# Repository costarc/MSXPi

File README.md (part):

# MSXPi

MSXPi is a hardware interface and software solution that lets MSX computers
control and use Raspberry Pi resources. The interface exposes I/O ports that
the MSX reads and writes, and the data appears on the Raspberry Pi side, where
a Python program (the *msxpi-server*) acts on it. Through it the MSX can reach
network drives, the internet, disk images, ROM archives, ChatGPT, an IRC
server, TCP/IP (via UNAPI) and the Raspberry Pi itself. A Raspberry Pi Zero W
or Zero 2 W is the recommended companion board.

MSXPi also exists as a virtual device for **openMSX**: the emulated MSX gets
the same commands and the same server, with no hardware at all. See
[Quick Start 2 - openMSX](#quick-start-2---openmsx-no-hardware-needed).

## 📖 The Book

The complete design and implementation of MSXPi is documented in a book:

**Anatomy of an Interface: MSXPi, a Case Study in Hardware/Software Co-Design**

It follows one real system, from the cartridge bus and the programmable logic to the
Python server on the Raspberry Pi and the applications on the MSX, and shows how each layer
was designed, built and tested. No MSX knowledge is assumed, and you do not need the board:
the whole system runs in the openMSX emulator on a PC.

The book covers:

* Design decisions and trade-offs
* Hardware architecture
* CPLD design (VHDL) and the Z80 bus interface
* Software implementation: Z80 assembly on the MSX, Python on the Raspberry Pi
* The LINK2 protocol and interface specifications
* Testing on real hardware and in openMSX
* Engineering lessons learned during development

### 👉 [Get the book on Amazon](https://link.amazon/B0eOuqOcq)

<sub>As an Amazon Associate, the author earns from qualifying purchases. Buying through this link
supports the MSXPi project at no extra cost to you.</sub>

> [!CAUTION]
> **Version 1.7.0 breaks compatibility with every earlier MSXPi ROM.**
> **Every MSXPi EEPROM must be rewritten with the 1.7.0 ROM** (`software/target/msxpi32k.rom`, written with
> `at28c256`, see [Step 2](#step-2---write-the-rom-to-the-eeprom-with-at28c256com)) before it is used with
> this release. Upgrade the whole set together: the ROM, the msxpi-server and the client commands (`.COM`
> files). Version 1.7.0 moves every transfer between the MSX and the Pi to LINK2, a new protocol with
> CRC-16 checked blocks; the new `.COM` files do not work with an older server. The CPLD firmware is
> unchanged (v1.6). To stay on an older ROM, use the server from the matching `release/vX.Y` branch.

Version 1.7.0 is the current release. What changed is in
[Release_Notes](Release_Notes); how to use everything is in the
[documents](documents) folder.

> **Notice: online gaming is in alpha testing.** The online games (PLAYNET and MCHAT game invitations,
> for example Konami's Soccer over the Internet) are experimental and **not ready for end users yet**.
> They have only been tested between emulators, expect bugs and missing pieces, and the files, commands and
> protocols may still change. Try them if you want to help test, but do not rely on them.
>
> `MCHAT` plays through the MSXPi when there is one, and over TCP/IP UNAPI (InterNestor Lite on the MSXPi's Ethernet, or a
> hardware stack such as GR8NET) when there is not. `MCHAT /T` forces TCP/IP even with an MSXPi. TCP/IP play needs a memory
> mapper (MSR or Nextor); see the users' guide section "Online games" for the requirements.

**CPLD firmware.** Version 1.7.0 uses the v1.6 CPLD firmware; a board already on
v1.6 needs no CPLD change. On older CPLD firmware the 1.7.0 ROM still works, using
the slower polled transfers.

**About the DOS.** MSXPi's own ROM contains **MSX-DOS 1 (1.03) only**. It does not
contain Nextor or MSX-DOS 2. MSXPi *coexists* with them: Nextor or MSX-DOS 2 come
from another disk interface in the same MSX (for example a MegaFlashROM SCC+ SD),
and MSXPi's commands, BASIC extension and UNAPI work alongside them. The
EEPROM holds two ROMs, picked with the bank jumper: MSX-DOS 1 (**BANK2**) or
the BIOS only - `CALL MSXPI` and the Ethernet UNAPI in ROM, no disk system
(**BANK1**) - for use next to Nextor / MSX-DOS 2. With the MSX-DOS 1 ROM the
Ethernet UNAPI driver is loaded from disk (`ETHUNAPI.COM`).

Contents

1. [How the pieces fit together](#how-the-pieces-fit-together)
2. [Quick Start 1 - Real hardware](#quick-start-1---real-hardware-msxpi-interface--raspberry-pi)
3. [Quick Start 2 - openMSX](#quick-start-2---openmsx-no-hardware-needed)
4. [Using MSXPi: the p commands](#using-msxpi-the-p-commands)
5. [Bugs and known limitations](#bugs-and-known-limitations)
6. [Repository structure](#repository-structure)

How the pieces fit together
===========================

    Real hardware:
    MSX  <-- I/O ports $56 $57 $5A -->  MSXPi interface  <-- GPIO -->  Raspberry Pi
    (p.com, pcopy, msxarch,             (CPLD + EEPROM with            (msxpi-server.py,
     BASIC CALL MSXPI, ROM BIOS)         the MSXPi ROM)                 Python 3)

    openMSX:
    MSX  <-- I/O ports $56 $57 $5A -->  MSXPiDevice      <-- TCP :5000 --> msxpi-server.py
                                        (emulated CPLD)                    (on your PC)

* **MSX side** - the ROMs in the interface's 32 KB EEPROM and the `.COM`
  programs that you copy to your MSX disk or SD card. The EEPROM image,
  `msxpi32k.rom`, holds two 16 KB ROMs:
  * `msxpibios.rom` - MSXPi BIOS, MSX-DOS 1 disk driver, `CALL MSXPI` for
    BASIC (the Ethernet UNAPI driver no longer fits here: load
    `ETHUNAPI.COM` for TCP/IP);
  * `msxpibas.rom` - the BIOS without the disk system: `CALL MSXPI` and the
    Ethernet UNAPI.
* **Interface** - a CPLD decodes ports $56/$57/$5A and shifts bytes to and
  from the Pi; since v1.6 it also holds the Z80 /WAIT line while a byte is in
  flight, so the MSX can move data with INIR/OTIR.
* **The link** - since 1.7.0 every transfer uses LINK2: framed blocks with a
  CRC-16 (CCITT-FALSE), acknowledged one by one and resent when damaged
  (`documents/LINK2-DESIGN.md`).
* **Server side** - `msxpi-server.py`, which runs on the Pi (GPIO link) or on
  your PC next to openMSX (TCP socket link). Everything it needs lives in one
  folder, the *MSXPi home directory*: `/home/pi/msxpi`.

Quick Start 1 - Real hardware (MSXPi interface + Raspberry Pi)
==============================================================

You will need:

* An MSXPi interface (built from `hardware/`; assembly notes in
  `documents/MSXPi Assembly Instructions.txt`) with an AT28C256 EEPROM.
* A Raspberry Pi Zero W / Zero 2 W (not a Pico - it cannot run Linux), with
  the 40-pin header on the side that matches your PCB, a micro SD card of 8 GB
  or more, and a PC to prepare it.
* An MSX with a disk or SD interface running MSX-DOS 1, MSX-DOS 2 or Nextor
  (MSXPi itself only has MSX-DOS 1 in its ROM; MSX-DOS 2 / Nextor must come
  from that other interface),
  and a way to copy files from your PC onto that disk. A second disk interface
  (Nextor / MSX-DOS 2) next to MSXPi is the best way to use it.
* Only if the CPLD is not programmed yet: an Altera USB-Blaster and Quartus
  13.0 SP1 on Windows.

Do the steps in order. Each ends with a check, so you know where a problem is.

### Step 1 - Program the CPLD (skip if it is already programmed)

1. Connect the USB-Blaster to the JTAG connector of the interface. The
   interface must be in the MSX slot and the MSX switched on.
2. In Quartus: Tools -> Programmer, mode JTAG, *Add File*, pick the `.pof` for
   your board, tick *Program/Configure* and *Verify*, *Start*.

   | Board | File (in `hardware/CPLD_Project`) |
   |---|---|
   | V1.3 Rev.1 (and boards built for v1.3 to v1.5) | `MSXPi_v1.6.pof` |
   | V1.1 Rev.1, V1.2.1b | `v1.1/MSXPi_v1.6_wait.pof` |
   | v0.8.2 / v1.0 (PCB v0.7 Rev.7) | `v0.8.2/MSXPi_v1.6_polled.pof` |

3. **Check:** in MSX BASIC, `PRINT INP(&H57)` must not print 254 or 255 (that
   means no CPLD answered); `p ver` shows the same build ID in readable form later. Older boards need a few extra settings - see
   `hardware/CPLD_Project/LEGACY_BOARDS.md` and `documents/Legacy Support.odt`.

### Step 2 - Write the ROM to the EEPROM with AT28C256.COM

The EEPROM (32 KB) holds `msxpi32k.rom`: two 16 KB ROMs, one per bank. It is
written from the MSX itself, so you need a working MSX with a disk drive and
the interface plugged in. The Raspberry Pi does not need to be attached yet.

| Bank jumper (as on the PCB) | EEPROM half | ROM | The MSX gets |
|---|---|---|---|
| **BANK2** (EEPROM A14 = CPU A15) | lower | `msxpibios.rom` | MSX-DOS 1 from the Pi, `CALL MSXPI` (Ethernet UNAPI from `ETHUNAPI.COM`) |
| **BANK1** (EEPROM A14 = CPU A14) | upper | `msxpibas.rom` | `CALL MSXPI` and Ethernet UNAPI, no disk system and no extra drives |

1. Copy `software/target/at28c256.com` and `software/target/msxpi32k.rom` to
   your MSX disk or SD card. (Both are also on the MSXPi boot disk.)
2. Set the bank jumper to **BANK2**. The EEPROM can only be programmed in
   that position: the chip's write-protection commands only reach the right
   addresses when its A14 follows CPU A15.
3. Boot MSX-DOS (from your disk interface) and list the ROMs the tool can see:

        at28c256 /i

   If the interface already holds a bootable ROM, remove its enable jumper
   (`SLTSL`, `CS12` on some boards) first, otherwise the MSX finds it, boots
   from it and the tool cannot write. Note the slot number of the interface.
4. Write the ROM (2 is the slot number here; use yours):

        at28c256 /s 2 msxpi32k.rom

   Always write the whole 32 KB file in one go: the tool erases the entire
   chip before writing, so writing one 16 KB ROM on its own wipes the other
   bank. The tool write-protects the EEPROM (software data protection) when
   it is done. If your chip fails to program, repeat with `/r`, which writes
   slowly.
5. Switch the MSX off and set the jumpers for how you will use it:

   * **Booting MSX-DOS 1 from a disk image on the Pi:** close `SLTSL`, bank
     jumper on **BANK2**. The Pi must finish booting first, so the first cold
     boot takes a few minutes. Press ESC during boot to go straight to BASIC.
   * **With another disk interface (recommended):** close `SLTSL`, bank
     jumper on **BANK1**, and put MSXPi in a higher slot than the disk
     interface. The MSX boots Nextor / MSX-DOS 2 from the other interface;
     MSXPi adds no drives and uses almost no memory, and `CALL MSXPI` in
     BASIC and the Ethernet UNAPI (in this ROM) are available.
   * **MSXPi ROM off:** remove `SLTSL`. MSXPi then works only through the
     `.COM` commands - no `CALL MSXPI`; for TCP/IP load `ETHUNAPI.COM`.

   The EEPROM answers in every page of its slot, so the bank that is not
   selected appears at 8000h. The two ROMs are built to tolerate each other
   there; always write them together, from the same `msxpi32k.rom`.
6. **Check:** in BASIC, `CALL MSXPIVER` prints the ROM version; with BANK1 it
   ends in "(no DOS)".

### Step 3 - Prepare the Raspberry Pi

Install a fresh Raspberry Pi OS Lite and run the MSXPi setup script. (The
old ready-made SD card image is no longer offered.)

1. Write *Raspberry Pi OS Lite (32-bit)* to the SD card with Raspberry Pi
   Imager (https://www.raspberrypi.com/software). In its settings choose user
   name `pi`, enable SSH and enter your WiFi details.
2. Boot the Pi, log in (SSH, or keyboard and HDMI) and run:

        wget https://tinyurl.com/MSXPi-Setup
        chmod 755 MSXPi-Setup
        bash ./MSXPi-Setup

   The script checks the Pi, the network and the clock, installs everything
   below, starts the server, checks that it runs, and reboots (a few minutes).
   It asks which board you have; to skip the question add `--board v1.3`,
   `--board v1.1` or `--board old` (see the table below). `--help` lists the
   other options (WiFi, `--no-reboot`, ...). It is safe to run again: it
   updates the server and repairs what is missing, and never overwrites
   `msxpi.ini`.

What the setup gives you (check it, or do it by hand):

* **Python 3** with the modules `requests`, `fs` and `RPi.GPIO`. `fs` needs
  `pkg_resources`, so a `setuptools` older than version 81 must be present
  (`python3 -m pip install fs "setuptools<81" --break-system-packages` if you do it
  by hand). The packages `unar`, `lhasa`, `unzip`, `mpv`, `alsa-utils` and
  `smbclient` are for unpacking archives, playing audio and reading network
  shares; `iptables` gives the MSX its network; `gcc` builds the native GPIO
  engine. PChess also needs the Python package `chess`
  (`requirements-pchess.txt`); the rest of the server works without it.
* **The MSXPi home directory `/home/pi/msxpi`**, owned by user `pi`. The path is
  built into the server (the environment variable `MSXPI_HOME` overrides it).
  It holds:

  | File | Purpose |
  |---|---|
  | `msxpi-server.py` and the `msxpi_*.py` modules (`msxpi_cmd_*.py`, `msxpi_transport.py`, `msxpi_settings.py`, ...), `mapper_detect.py` | the server and its modules |
  | `native/` | the native GPIO library `libmsxpi_gpio.so`, built on the Pi (without it the server falls back to slower Python GPIO and says so in its log) |
  | `msxpi.ini` | your settings, see below |
  | `disks/msxpiboot.dsk`, `disks/tools.dsk` | drives A: and B: for the MSX-DOS 1 boot mode |
  | `msxpi-monitor`, `msxpi-tcpip-setup.sh`, `update.sh` | helpers |

* **A systemd service** (`msxpi-monitor`) that starts the server at boot. To
  watch it work, run it by hand: `cd /home/pi/msxpi && python3 msxpi-server.py`.
* **msxpi.ini**, copied from the template that matches your PCB
  (`software/Server/Python/src`):

  | Board | Template |
  |---|---|
  | V1.3 (and later) | `msxpi-JumperRight.ini` |
  | V1.1 Rev.0 | `msxpi-JumperRight_PCBV1.1Rev.0.ini` |
  | Older boards | `msxpi-JumperLeft.ini` |

  A board **without** the shutdown push-button needs `var RPI_SHUTDOWN=none`.
  Optional keys: `OPENAIKEY` and `OPENAIMODEL` (ChatGPT), `RAPIDAPIKEY`,
  `FINNHUBKEY`, `TWELVEDATAKEY`, `ALPHAVANTAGEKEY` (stock quotes),
  `WIFISSID`, `WIFIPWD`, `WIFICOUNTRY`. From the MSX you can change any of
  them with `p set NAME value`.

Insert the SD card, plug the Pi into the interface **with its component side
facing you**, and switch the MSX on. The interface LED lights when the server
is running.

### Step 4 - Copy the MSX-side programs

Copy the contents of `software/target` (at least `p.com`, `pcopy.com`,
`msxarch.com`, `msxarch.ini`, `LOADROM.COM`, `ETHUNAPI.COM`, `INL.CFG` and
the `.BAS` programs) to your MSX disk or SD card. They must all come from the
same release as the ROM and the server.

**Check:** at the MSX-DOS prompt type

        p ver

It prints the board (build ID, CPLD, `/WAIT` yes or no) and the server version.
"Connection error" means the Pi is still booting (the first boot may take three
minutes), the interface is not seated, or the ROM and server versions do not
match. Press CTRL+ESC, wait five seconds, and try again. A "protocol error"
means the server is older than 1.7.0 and cannot speak LINK2: update the server.

### Step 5 - Connect to WiFi and the network

        p set WIFISSID Your Wifi Name
        p set WIFIPWD YourWifiPassword
        p wifi set
        p reboot

`p wifi` alone lists the interfaces and addresses. For TCP/IP programs (UNAPI:
InterNestor Lite, telnet, HGET) the MSX needs the MSXPi Ethernet UNAPI driver,
and the Pi builds the network behind it with `msxpi-tcpip-setup.sh` when the
server starts. If the Pi had no default route at boot, run `p netreset`. Then,
depending on how the MSX was started:

| ROM bank / DOS | Type, in this order |
|---|---|
| **BANK2**, MSX-DOS 1 booted from MSXPi | `MSR I`, `ETHUNAPI`, `INL I` |
| **BANK1**, MSX-DOS 1 from another interface | `MSR I`, `INL I` |
| **BANK1**, Nextor or MSX-DOS 2 | `RAMHELPR I`, `INL I` |

then `HOST GOOGLE.COM`. With BANK1 the driver is in the ROM and `ETHUNAPI`
refuses to load. Under MSX-DOS 1 never run `RAMHELPR`: `MSR` installs the RAM
helper itself and fails if one is already there.

`HOST` printing an address means the whole path works. `p wlanreset` resets the
Pi's WiFi. Details: `software/UNAPI/README.md`.

### Step 6 - Try it

        p dir /home/pi/msxpi
        p run uname -a
        pcopy m:p.com
        msxarch                     (browse and start ROM games from the network)
        LOADROM game.rom /N
        p chatgpt Tell me a fun fact about MSX

### Updating

* MSX disk (the `.COM` files): run `msxpiupd.bat` (network required).
* To update from another git branch (client files, ROMs and server), give its name: `msxpiupd feature/name`.
  Without a name it is master. Files that exist only in the branch are not copied.
* Server: run the setup script again, from the Pi or from the MSX:

        p run wget https://tinyurl.com/MSXPi-Setup
        p run chmod 755 MSXPi-Setup
        p run sudo ./MSXPi-Setup

* ROM: the updater downloads it but never writes it - repeat Step 2.

Update all three together: the ROM, the server and the clients (`.COM` files, including `playnet.com`, `playnet.ovl`
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
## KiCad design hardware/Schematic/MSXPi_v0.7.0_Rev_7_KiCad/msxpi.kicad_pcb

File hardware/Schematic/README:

1.1.Rev.1 - Added jumpers to switch also SPI-RDY signal
            Added line for Reset signal - may not be safe for all MSX models
1.1.Rev.0 - Replaced Raspberry Pi mounting holes by 40 Pin Socket
      - Added jumpers to select between bit-bang GPIO and hardware GPIO pins (future use)
1.0.3 - Shifted PCB holes to better fit in Patola (Brazilian) case & added 3rd mounting hole
1.0.2 - Changed footprint to smaller size to help reducing manufacturing costs
1.0.1 - Changed ROM from 27C256 to AT28C256 with hability to be programmed from MSX-DOS
1.0 - PCB Changes from Rev.7

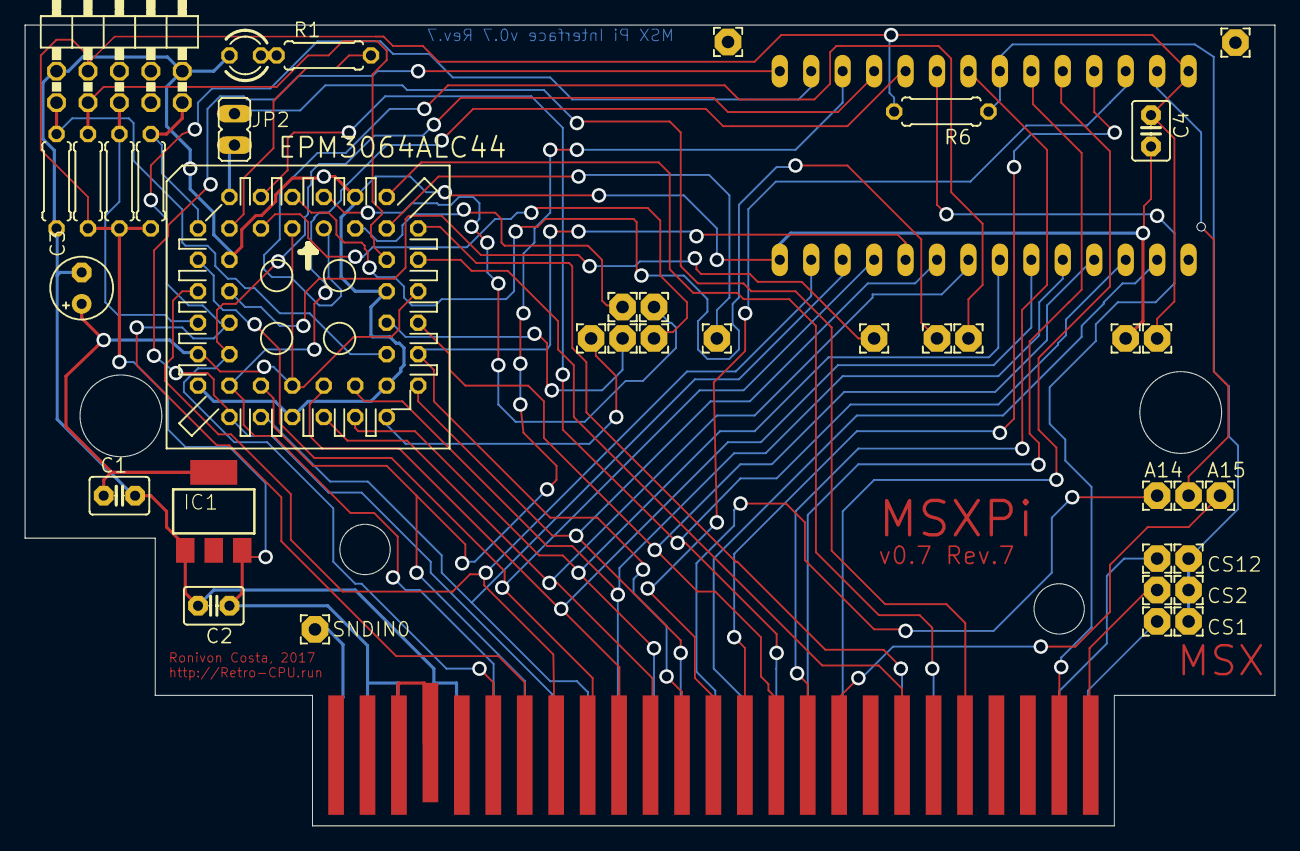
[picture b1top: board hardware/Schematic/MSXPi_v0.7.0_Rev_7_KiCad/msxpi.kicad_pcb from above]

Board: 2 copper layers, 101.0 x 64.7 mm, 40 parts (1 on the bottom side), 55 nets.

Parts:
+5V0: 2,15_1,0
A14, A15: 2,15_1,0
BUF1, BUF2: 2,15_1,0
C1, C2, C4: C2.5-3
C3: E2,5-5
CS1, CS2, CS12: 2,15_1,0
EPM3064ALC44: EPM3064S44; PLCC-S44
GND0, GND4, GND9, GND10, GND11: 2,15_1,0
IC1: LD117AS33TR; SOT223
JP2: JP1
JP6: MSXCART1; MSXCART
JP7: 2X05_90
LED1: LED3MM
PAD1, PAD2, PAD8, PAD9: 2,15_1,0
R1, R2, R3, R4, R5, R6: 0207_7
ROMOE1, ROMOE2, ROMOE3: 2,15_1,0
ROM_OE0: 2,15_1,0
SNDIN0: 2,15_1,0
SPI_CS_GPIO21: 2,15_1,0
UNK27C256: DIL28

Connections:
+5V: +5V0.1, C2.1, C4.1, IC1.3, JP6.45, JP6.47, JP7.4, R3.1, R4.1, R5.1, R6.2, UNK27C256.28
A0: EPM3064ALC44.31, JP6.28, UNK27C256.10
A1: EPM3064ALC44.29, JP6.27, UNK27C256.9
A2: EPM3064ALC44.24, JP6.30, UNK27C256.8
A3: EPM3064ALC44.26, JP6.29, UNK27C256.7
A4: EPM3064ALC44.25, JP6.32, UNK27C256.6
A5: EPM3064ALC44.27, JP6.31, UNK27C256.5
A6: EPM3064ALC44.33, JP6.22, UNK27C256.4
A7: EPM3064ALC44.4, JP6.21, UNK27C256.3
A8: JP6.24, UNK27C256.25
A9: JP6.17, UNK27C256.24
A10: JP6.20, UNK27C256.21
A11: JP6.19, UNK27C256.23
A12: JP6.23, UNK27C256.2
A13: JP6.26, UNK27C256.26
A14: A14.1, JP6.25
A15: A15.1, JP6.18
BUSDIR: JP2.1, JP6.10
CS1: CS1.1, JP6.1
CS2: CS2.1, JP6.2
CS12: CS12.1, JP6.3
D0: EPM3064ALC44.9, JP6.34, UNK27C256.11
D1: EPM3064ALC44.20, JP6.33, UNK27C256.12
D2: EPM3064ALC44.11, JP6.36, UNK27C256.13
D3: EPM3064ALC44.18, JP6.35, UNK27C256.15
D4: EPM3064ALC44.14, JP6.38, UNK27C256.16
D5: EPM3064ALC44.21, JP6.37, UNK27C256.17
D6: EPM3064ALC44.16, JP6.40, UNK27C256.18
D7: EPM3064ALC44.19, JP6.39, UNK27C256.19
GND: C1.2, C2.2, C3.-, C4.2, EPM3064ALC44.10, EPM3064ALC44.17, EPM3064ALC44.22, EPM3064ALC44.30, EPM3064ALC44.36, EPM3064ALC44.42, GND0.1, IC1.1, JP6.41, JP6.43, JP7.2, JP7.10, LED1.K, R2.1, UNK27C256.14
IORQ: EPM3064ALC44.40, JP6.11
MSXR1: EPM3064ALC44.6, JP2.2
unnamed: JP6.44, JP6.46
unnamed: LED1.A, R1.1
unnamed: EPM3064ALC44.8, R1.2
PIN1: EPM3064ALC44.1, GND4.1
PIN2: EPM3064ALC44.2, GND9.1
PIN43: EPM3064ALC44.43, GND10.1
PIN44: EPM3064ALC44.44, GND11.1
PI_RDY_GPIO25: EPM3064ALC44.12, PAD2.1
RD: EPM3064ALC44.37, JP6.14
ROM_A14: ROM_OE0.1, UNK27C256.27
ROM_OE: R6.1, ROMOE1.1, ROMOE2.1, ROMOE3.1, UNK27C256.22
SLTSL: JP6.4, UNK27C256.20
SNDIN: JP6.49, SNDIN0.1
SPI_CS_GPIO21: EPM3064ALC44.28, SPI_CS_GPIO21.1
SPI_MISO_GPIO12: EPM3064ALC44.41, PAD1.1
SPI_MOSI_GPIO16: EPM3064ALC44.5, PAD9.1
SPI_SCLK_GPIO20: EPM3064ALC44.34, PAD8.1
TCK: EPM3064ALC44.32, JP7.1, R2.2
TDI: EPM3064ALC44.7, JP7.9, R5.2
TDO: EPM3064ALC44.38, JP7.3, R3.2
TMS: EPM3064ALC44.13, JP7.5, R4.2
VCCIO: C1.1, C3.+, EPM3064ALC44.3, EPM3064ALC44.15, EPM3064ALC44.23, EPM3064ALC44.35, IC1.4
WR: EPM3064ALC44.39, JP6.13

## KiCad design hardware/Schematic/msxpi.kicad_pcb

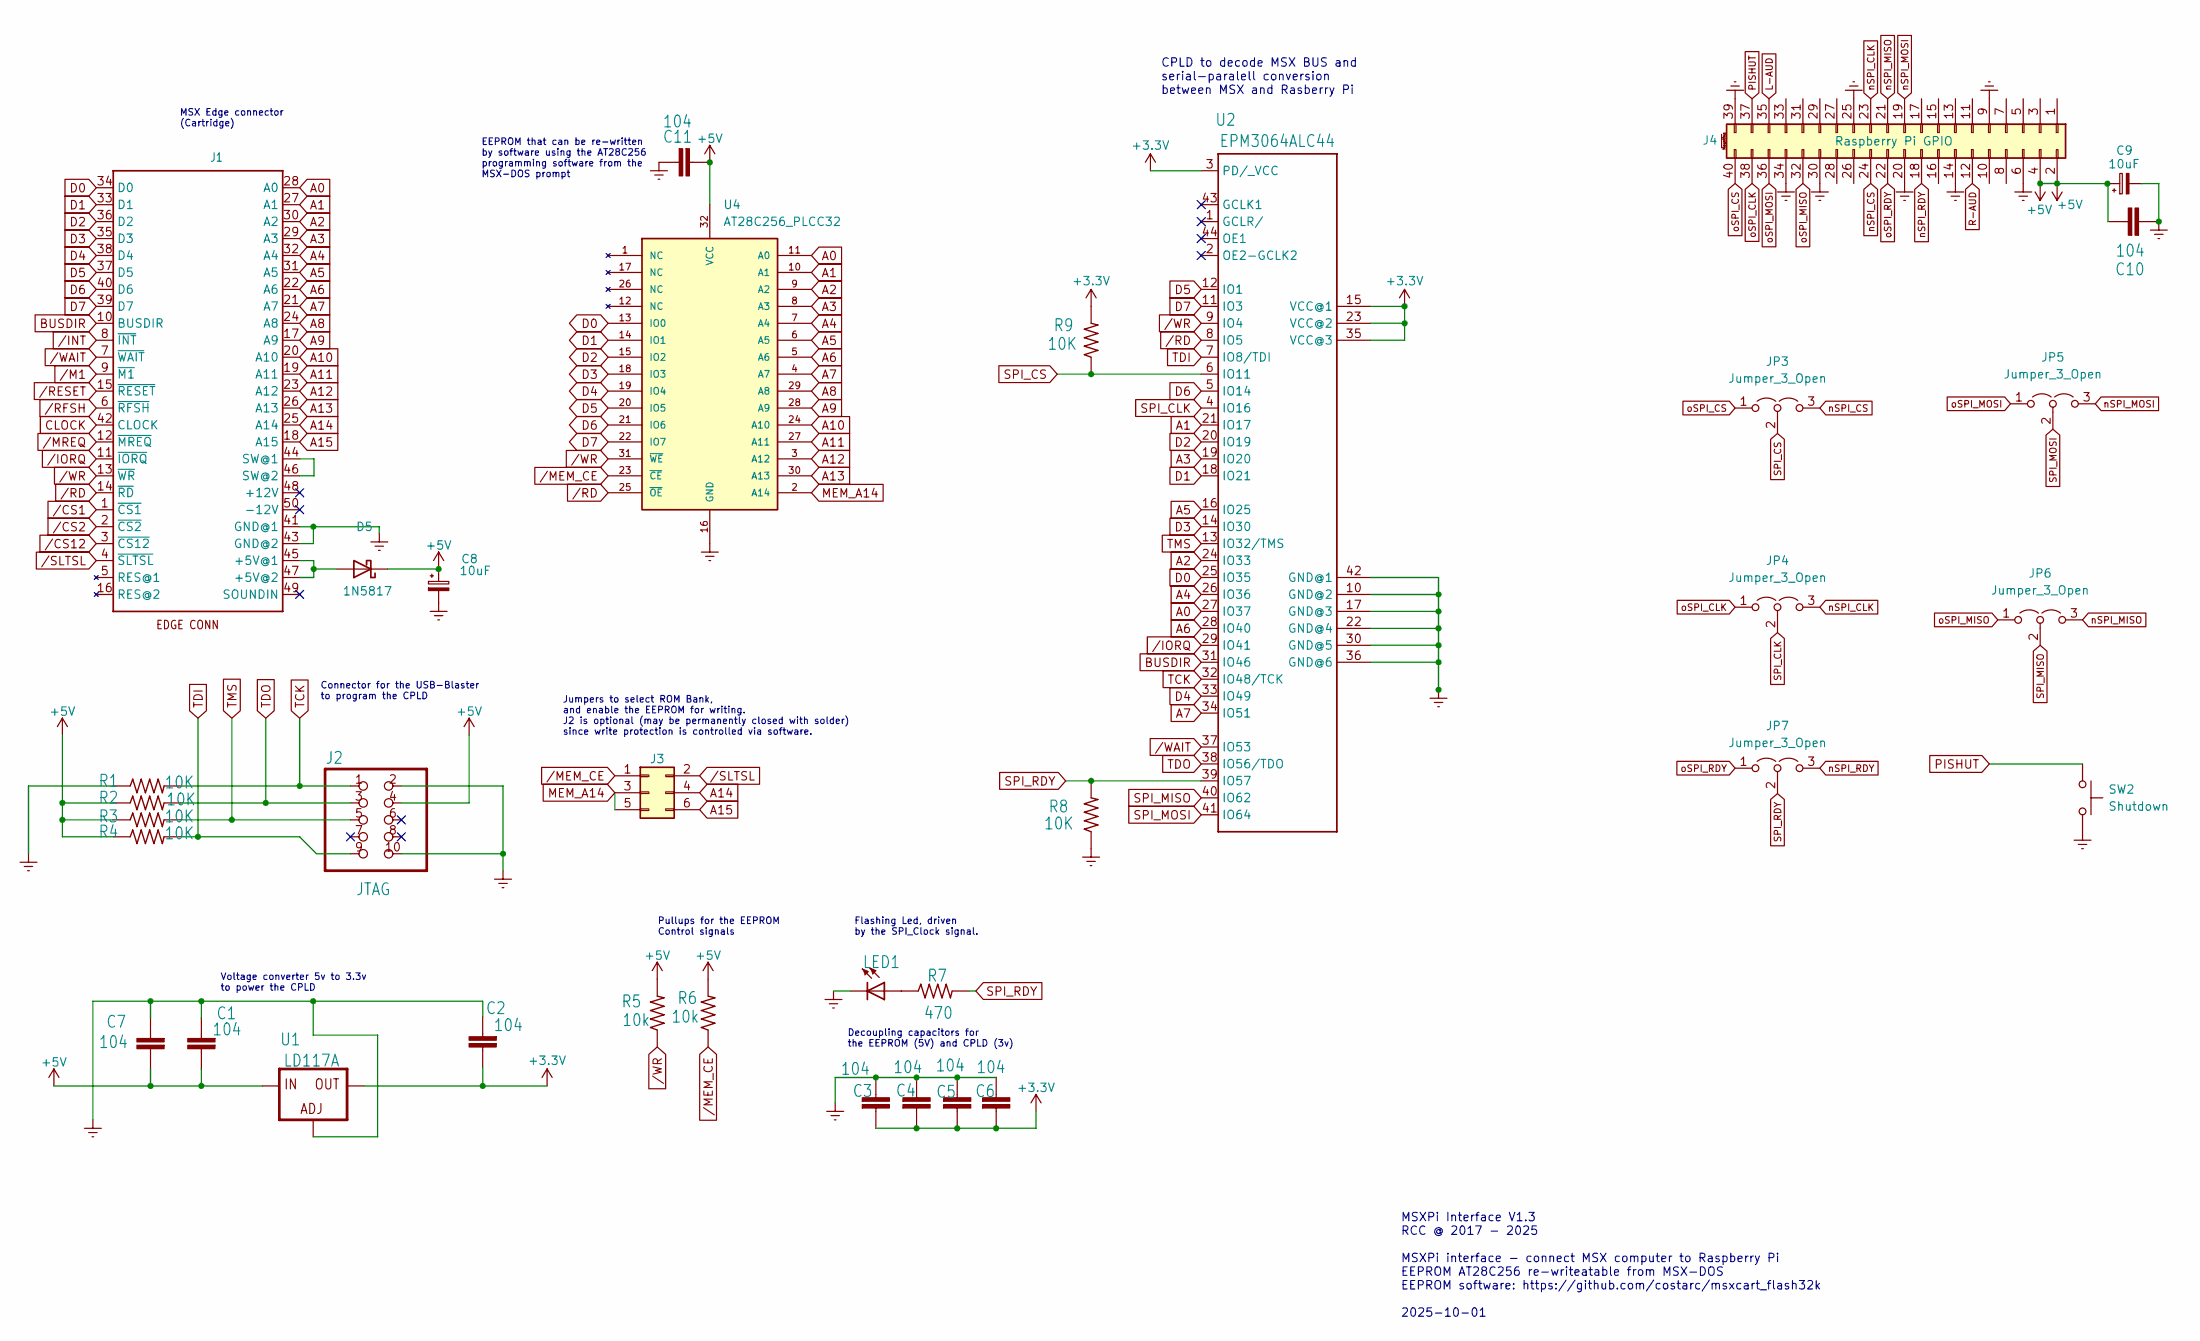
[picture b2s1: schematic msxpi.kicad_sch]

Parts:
C1, C2, C3, C4, C5, C6, C7, C10, C11: 104; C2.5-3
C8, C9: 10uF; CP_Radial_D5.0mm_P2.00mm
D5: 1N5817; D_DO-41_SOD81_P10.16mm_Horizontal
J1: MSXCART1; MSX_CART_SW_Official_3Holes
J2: JTAG; IDC-Header_2x05_P2.54mm_Horizontal
J3: ROM_SWITCH; PinHeader_2x03_P2.54mm_Vertical
J4: Raspberry Pi GPIO; PinSocket_2x20_P2.54mm_Vertical
JP3, JP4, JP5, JP6, JP7: Jumper_3_Open; SolderJumper-3_P1.3mm_Open_Pad1.0x1.5mm
LED1: LED3MM
R1, R2, R3, R4, R8, R9: 10K; 0207_7
R5, R6: 10k; 0207_7
R7: 470; 0207_7
SW2: Shutdown; SW_PUSH_6mm_2Holes
U1: LD117A; SOT-223-3_TabPin2
U2: EPM3064ALC44; PLCC-S44
U4: AT28C256_PLCC32; PLCC-32_THT-Socket

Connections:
+3.3V: C2.1, C3.2, C4.2, C5.2, C6.2, R9.2, U1.2 (OUT), U2.3 (PD/_VCC), U2.15 (VCC@1), U2.23 (VCC@2), U2.35 (VCC@3)
+5V: C1.1, C7.1, C8.1, C9.1, C10.1, C11.1, D5.1 (K), J2.4, J4.2, J4.4, R2.1, R3.1, R4.1, R5.2, R6.2, U1.3 (IN), U4.32 (VCC)
A0: J1.28 (A0), U2.27 (IO37), U4.11 (A0)
A1: J1.27 (A1), U2.21 (IO17), U4.10 (A1)
A2: J1.30 (A2), U2.24 (IO33), U4.9 (A2)
A3: J1.29 (A3), U2.19 (IO20), U4.8 (A3)
A4: J1.32 (A4), U2.26 (IO36), U4.7 (A4)
A5: J1.31 (A5), U2.16 (IO25), U4.6 (A5)
A6: J1.22 (A6), U2.28 (IO40), U4.5 (A6)
A7: J1.21 (A7), U2.34 (IO51), U4.4 (A7)
A8: J1.24 (A8), U4.29 (A8)
A9: J1.17 (A9), U4.28 (A9)
A10: J1.20 (A10), U4.24 (A10)
A11: J1.19 (A11), U4.27 (A11)
A12: J1.23 (A12), U4.3 (A12)
A13: J1.26 (A13), U4.30 (A13)
A14: J1.25 (A14), J3.4
A15: J1.18 (A15), J3.6
BUSDIR: J1.10 (BUSDIR), U2.31 (IO46)
CLOCK: J1.42 (CLOCK)
D0: J1.34 (D0), U2.25 (IO35), U4.13 (IO0)
D1: J1.33 (D1), U2.18 (IO21), U4.14 (IO1)
D2: J1.36 (D2), U2.20 (IO19), U4.15 (IO2)
D3: J1.35 (D3), U2.14 (IO30), U4.18 (IO3)
D4: J1.38 (D4), U2.33 (IO49), U4.19 (IO4)
D5: J1.37 (D5), U2.12 (IO1), U4.20 (IO5)
D6: J1.40 (D6), U2.5 (IO14), U4.21 (IO6)
D7: J1.39 (D7), U2.11 (IO3), U4.22 (IO7)
GNDREF: C1.2, C2.2, C3.1, C4.1, C5.1, C6.1, C7.2, C8.2, C9.2, C10.2, C11.2, J1.41 (GND@1), J1.43 (GND@2), J2.2, J2.10, J4.6, J4.9, J4.14, J4.20, J4.25, J4.30, J4.34, J4.39, LED1.K (C), R1.1, R8.1, SW2.2, U1.1 (ADJ), U2.10 (GND@2), U2.17 (GND@3), U2.22 (GND@4), U2.30 (GND@5), U2.36 (GND@6), U2.42 (GND@1), U4.16 (GND)
L-AUD: J4.35
MEM_A14: J3.3, J3.5, U4.2 (A14)
unnamed: D5.2 (A), J1.45 (+5V@1), J1.47 (+5V@2)
unnamed: J1.44 (SW@1), J1.46 (SW@2)
unnamed: LED1.A, R7.1
PISHUT: J4.37, SW2.1
R-AUD: J4.12
SPI_CLK: JP4.2 (C), U2.4 (IO16)
SPI_CS: JP3.2 (C), R9.1, U2.6 (IO11)
SPI_MISO: JP6.2 (C), U2.40 (IO62)
SPI_MOSI: JP5.2 (C), U2.41 (IO64)
SPI_RDY: JP7.2 (C), R7.2, R8.2, U2.39 (IO57)
TCK: J2.1, R1.2, U2.32 (IO48/TCK)
TDI: J2.9, R4.2, U2.7 (IO8/TDI)
TDO: J2.3, R2.2, U2.38 (IO56/TDO)
TMS: J2.5, R3.2, U2.13 (IO32/TMS)
nSPI_CLK: J4.23, JP4.3 (B)
nSPI_CS: J4.24, JP3.3 (B)
nSPI_MISO: J4.21, JP6.3 (B)
nSPI_MOSI: J4.19, JP5.3 (B)
nSPI_RDY: J4.18, JP7.3 (B)
oSPI_CLK: J4.38, JP4.1 (A)
oSPI_CS: J4.40, JP3.1 (A)
oSPI_MISO: J4.32, JP6.1 (A)
oSPI_MOSI: J4.36, JP5.1 (A)
oSPI_RDY: J4.22, JP7.1 (A)
/CS1: J1.1 (~CS1)
/CS2: J1.2 (~CS2)
/CS12: J1.3 (~CS12)
/INT: J1.8 (~INT)
/IORQ: J1.11 (~IORQ), U2.29 (IO41)
/M1: J1.9 (~M1)
/MEM_CE: J3.1, R6.1, U4.23 (~CE)
/MREQ: J1.12 (~MREQ)
/RD: J1.14 (~RD), U2.8 (IO5), U4.25 (~OE)
/RESET: J1.15 (~RESET)
/RFSH: J1.6 (~RFSH)
/SLTSL: J1.4 (~SLTSL), J3.2
/WAIT: J1.7 (~WAIT), U2.37 (IO53)
/WR: J1.13 (~WR), R5.1, U2.9 (IO4), U4.31 (~WE)

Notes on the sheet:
Decoupling capacitors for the EEPROM (5V) and CPLD (3v)
Flashing Led, driven by the SPI_Clock signal.
Jumpers to select ROM Bank, and enable the EEPROM for writing. J2 is optional (may be permanently closed with solder) since write protection is controlled via software.
EEPROM that can be re-written by software using the AT28C256 programming software from the MSX-DOS prompt
Pullups for the EEPROM Control signals
MSXPi Interface V1.3 RCC @ 2017 - 2025 MSXPi interface - connect MSX computer to Raspberry Pi EEPROM AT28C256 re-writeatable from MSX-DOS EEPROM software: https://github.com/costarc/msxcart_flash32k 2025-10-01
MSX Edge connector (Cartridge)
Connector for the USB-Blaster to program the CPLD
Voltage converter 5v to 3.3v to power the CPLD
CPLD to decode MSX BUS and serial-paralell conversion between MSX and Rasberry Pi

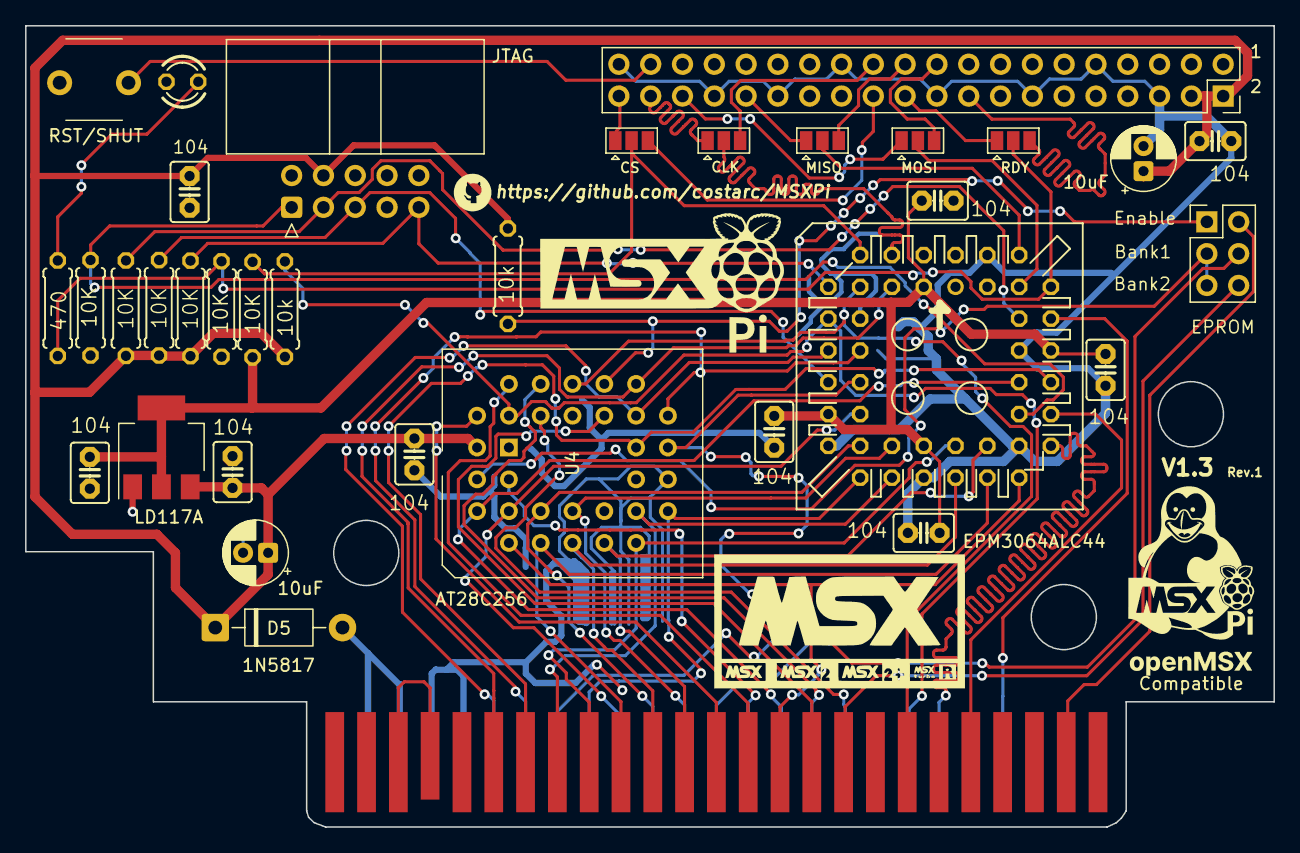
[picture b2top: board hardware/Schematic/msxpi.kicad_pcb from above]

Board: 2 copper layers, 99.7 x 64.0 mm, 35 parts (0 on the bottom side), 58 nets.

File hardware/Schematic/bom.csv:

Reference,Value,P/N or Link,Footprint,Qty
"C1,C2,C3,C4,C5,C6,C7,C10,C11",0.1uF,Multiple sources,Ceramic Capacitor code “104”,9
"C8,C9",10uF,https://www.aliexpress.com/item/1005002533909480.html,Capacitor_THT:CP_Radial_D5.0mm_P2.00mm,2
D5,1N5817,https://www.aliexpress.com/item/1005001552094086.html,Diode_THT:D_DO-41_SOD81_P10.16mm_Horizontal,1
J2,JTAG,https://www.aliexpress.com/item/1005005509699672.html,Connector_IDC:IDC-Header_2x05_P2.54mm_Horizontal,1
J3,ROM_SWITCH,https://www.aliexpress.com/item/1005006733621288.html,Connector_PinHeader_2.54mm:PinHeader_2x03_P2.54mm_Vertical,1
J4,Raspberry Pi GPIO,https://www.aliexpress.com/item/1005008966856219.html,PinSocket_2x20_P2.54mm_Vertical,1
LED1,LED3MM,Multiple sources,LED3MM,1
"R1,R2,R3,R4,R8,R9",10KOhm,https://www.aliexpress.com/item/32315929780.html,Resistor THT 6mm,6
"R5,R6",10kOhm,https://www.aliexpress.com/item/32315929780.html,Resistor THT 6mm,2
R7,470 Ohm,https://www.aliexpress.com/item/32317115890.html,Resistor THT 6mm,1
SW2,Shutdown/Reset,https://www.aliexpress.com/item/1005006804318686.html,Tactile Push Button 6x6x5 2Pin,1
U1,LD117A,Multiple sources / Recommended Mouser/Digikey,3v3 Regulator Package_TO_SOT_SMD:SOT-223-3,1
U2,EPM3064ALC44,Multiple sources / Recommended Mouser/Digikey,CPLD Altera EPM3064ALC44 PLCC Package,1
,Socket PLCC-44 DIP,https://www.aliexpress.com/item/1005006107285280.html,Socket for CPLD EPM3064ALC44 DIP,
U4,AT28C256_PLCC32,https://www.aliexpress.com/item/1005007853008289.html,EEPROM ATMEL AT28C256 PLCC Package,1
,Socket PLCC-32 DIP,https://www.aliexpress.com/item/1005006107285280.html,Socket for EEPROM AT28C256 PLCC DIP,

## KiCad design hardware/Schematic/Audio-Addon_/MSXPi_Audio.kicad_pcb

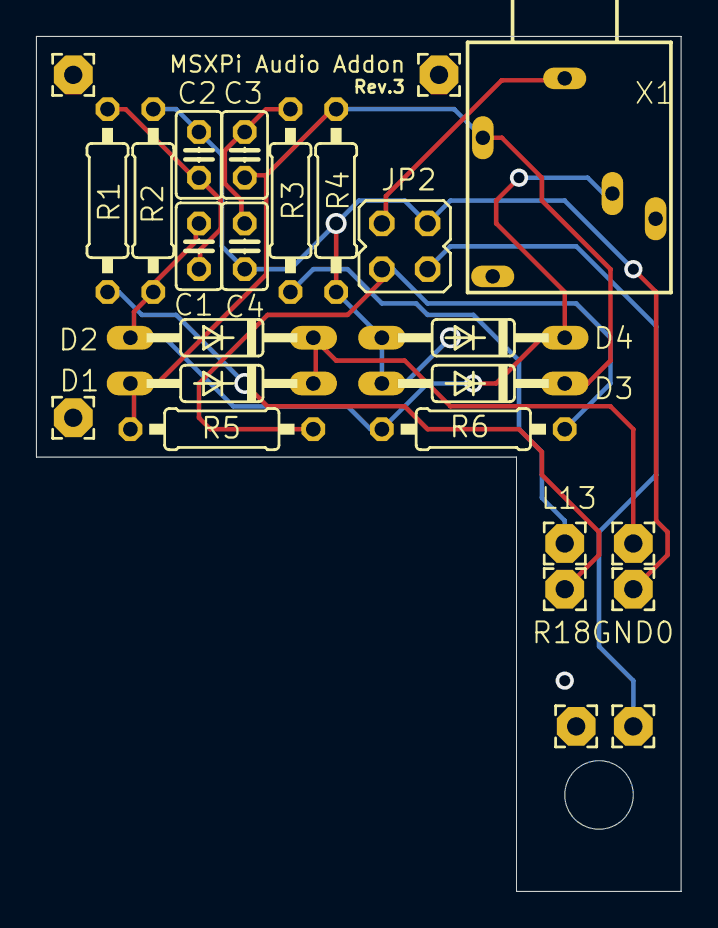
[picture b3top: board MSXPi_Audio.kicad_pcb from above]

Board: 2 copper layers, 35.8 x 47.5 mm, 26 parts (0 on the bottom side), 11 nets.

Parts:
@HOLE0: (no value)
C1, C2, C3, C4: C025-025X050
D1, D2, D3, D4: 1N4148DO35-10; DO35-10
GND0: 2,15_1,0
JP2: JP2Q
L13: 2,15_1,0
R1, R2, R3, R4, R5, R6: 0207_10
R18: 2,15_1,0
SNDIN0: 2,15_1,0
UNK1, UNK2, UNK3, UNK3V0, UNK5: 2,15_1,0
X1: 1503_09

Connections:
GND: C2.2, C4.2, D3.A, D4.A, GND0.1, JP2.3, R2.1, R4.1
LOUT_L: C3.2, D1.A, D3.C, R4.2, R5.1, X1.2
LOUT_R: C1.2, D2.A, D4.C, R2.2, R6.1, X1.5
unnamed: R1.1, R18.1
unnamed: JP2.2, R5.2, R6.2
unnamed: C1.1, C2.1, R1.2
unnamed: JP2.1, SNDIN0.1
unnamed: L13.1, R3.1
unnamed: C3.1, C4.1, R3.2
unnamed: JP2.4, X1.1
VCC: D1.C, D2.C, UNK3V0.1

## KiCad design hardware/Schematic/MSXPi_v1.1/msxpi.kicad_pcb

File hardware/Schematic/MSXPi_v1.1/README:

1.1.0 - Replaced Raspbery Pi mounting holes by 40 Pin Socket
      - Added jumpers to select between bit-bang GPIO and hardware GPIO pins
1.0.3 - Shifted PCB holes to better fit in Patola (Brazilian) case & added 3rd mounting hole
1.0.2 - Changed footprint to smaller size to help reducing manufacturing costs
1.0.1 - Changed ROM from 27C256 to AT28C256 with hability to be programmed from MSX-DOs
1.0 - PCB Changes from Rev.7

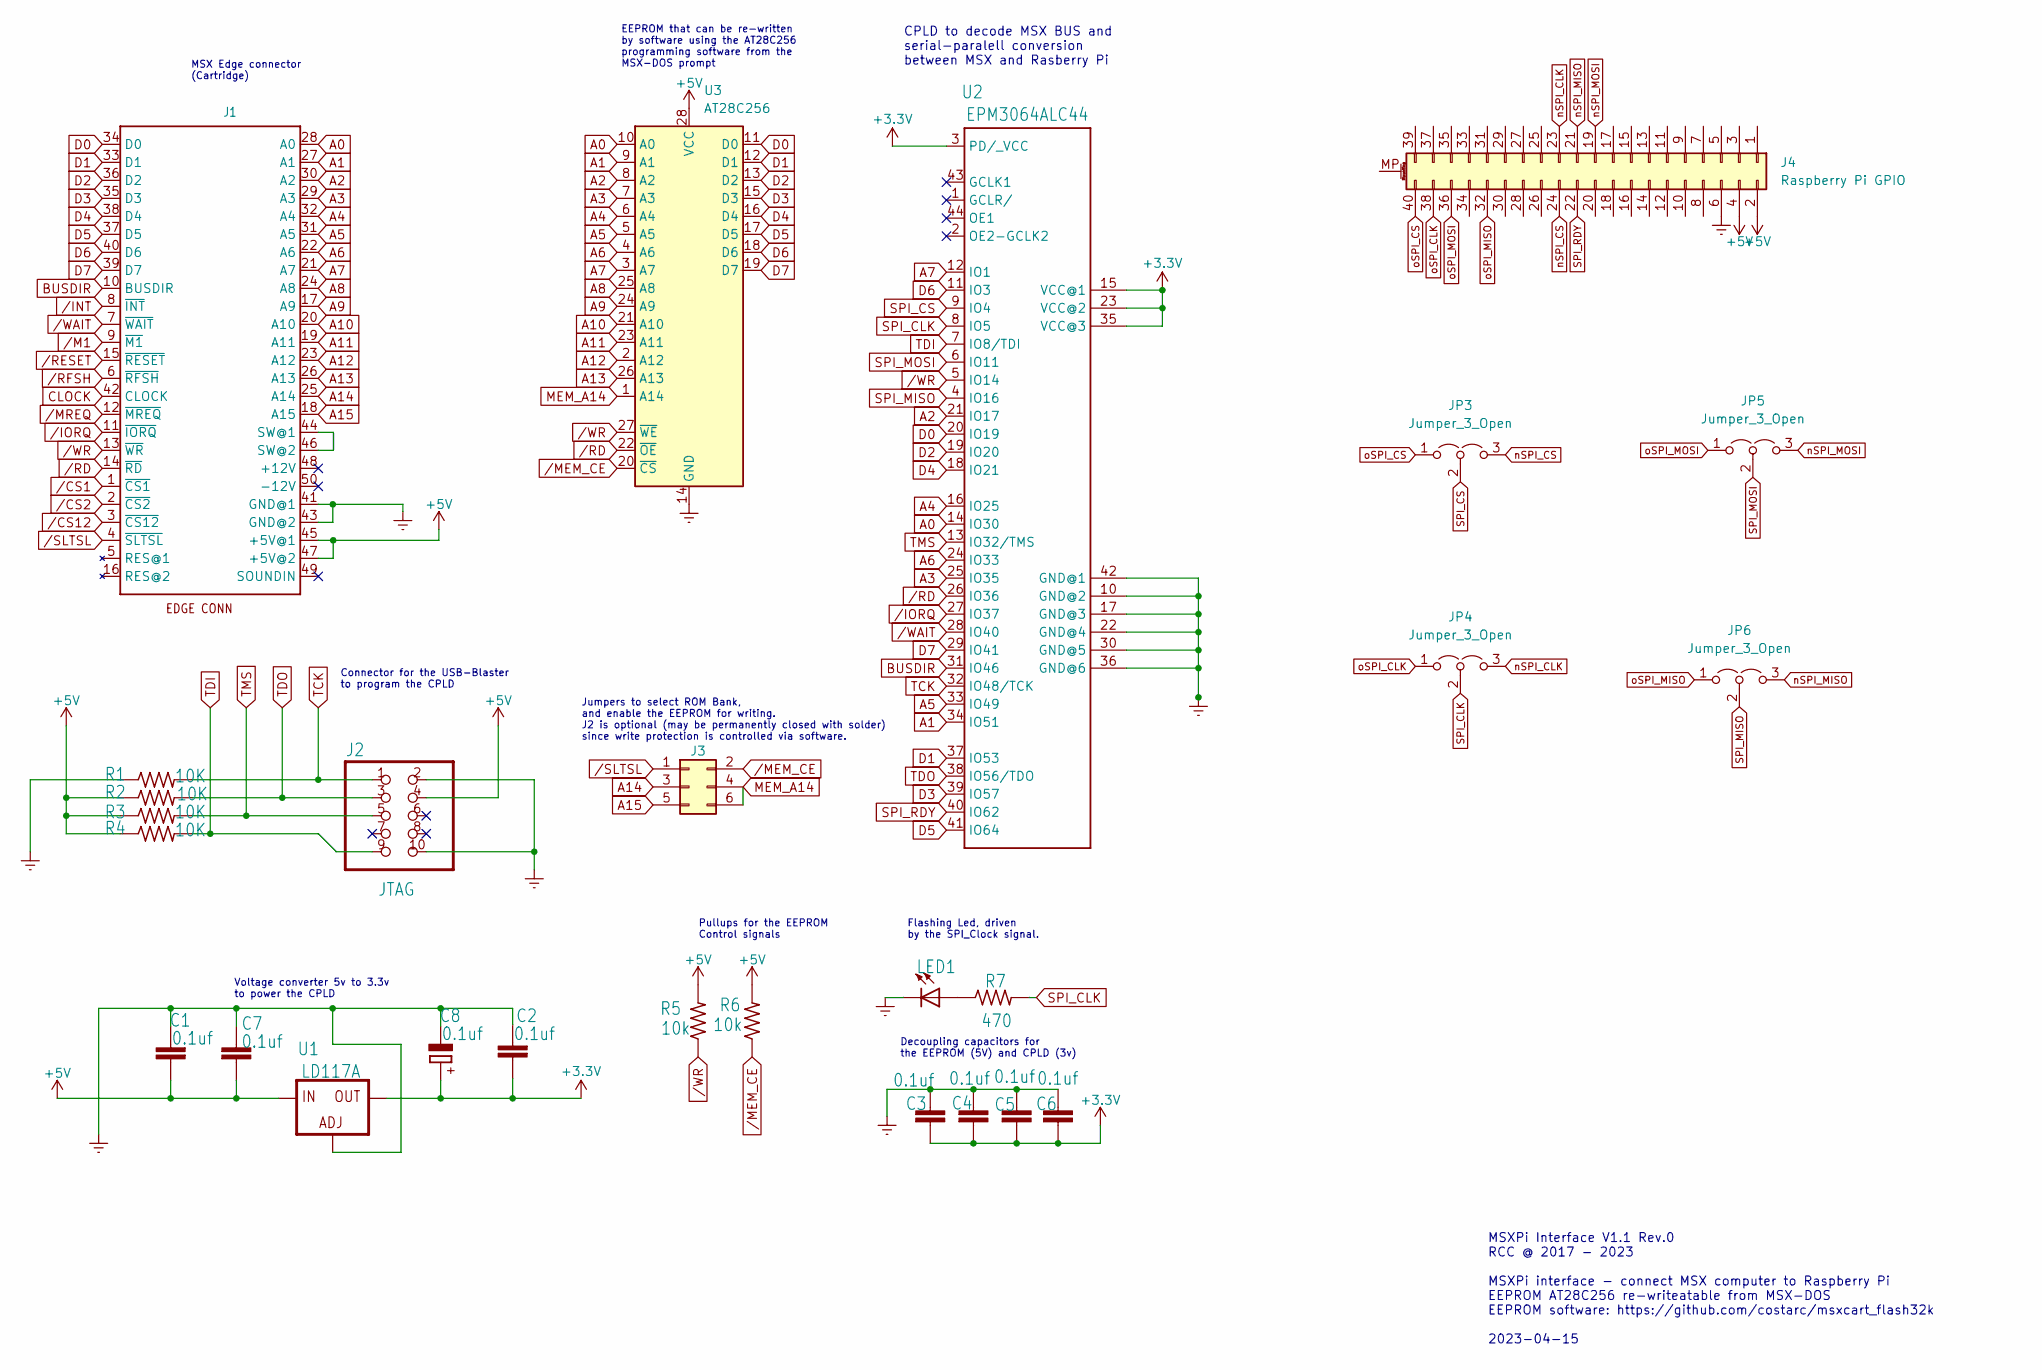
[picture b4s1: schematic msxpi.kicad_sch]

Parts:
C1, C2, C3, C4, C5, C6, C7: 0.1uf; C2.5-3
C8: 0.1uf; E2,5-5
J1: MSXCART1; MSX_CART_SW_Official_3Holes
J2: JTAG; IDC-Header_2x05_P2.54mm_Horizontal
J3: ROM_SWITCH; PinHeader_2x03_P2.54mm_Vertical
J4: Raspberry Pi GPIO; PinSocket_2x20_P2.54mm_Vertical
JP3, JP4, JP5, JP6: Jumper_3_Open; SolderJumper-3_P1.3mm_Open_Pad1.0x1.5mm
LED1: LED3MM
R1, R2, R3, R4: 10K; 0207_7
R5, R6: 10k; 0207_7
R7: 470; 0207_7
U1: LD117A; SOT-223-3_TabPin2
U2: EPM3064ALC44; PLCC-S44
U3: AT28C256; DIP-28_W15.24mm

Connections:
+3.3V: C2.1, C3.2, C4.2, C5.2, C6.2, C8.+, U1.2 (OUT), U2.3 (PD/_VCC), U2.15 (VCC@1), U2.23 (VCC@2), U2.35 (VCC@3)
+5V: C1.1, C7.2, J1.45 (+5V@1), J1.47 (+5V@2), J2.4, J4.2, J4.4, R2.1, R3.1, R4.1, R5.2, R6.2, U1.3 (IN), U3.28 (VCC)
A0: J1.28 (A0), U2.14 (IO30), U3.10 (A0)
A1: J1.27 (A1), U2.34 (IO51), U3.9 (A1)
A2: J1.30 (A2), U2.21 (IO17), U3.8 (A2)
A3: J1.29 (A3), U2.25 (IO35), U3.7 (A3)
A4: J1.32 (A4), U2.16 (IO25), U3.6 (A4)
A5: J1.31 (A5), U2.33 (IO49), U3.5 (A5)
A6: J1.22 (A6), U2.24 (IO33), U3.4 (A6)
A7: J1.21 (A7), U2.12 (IO1), U3.3 (A7)
A8: J1.24 (A8), U3.25 (A8)
A9: J1.17 (A9), U3.24 (A9)
A10: J1.20 (A10), U3.21 (A10)
A11: J1.19 (A11), U3.23 (A11)
A12: J1.23 (A12), U3.2 (A12)
A13: J1.26 (A13), U3.26 (A13)
A14: J1.25 (A14), J3.3
A15: J1.18 (A15), J3.5
BUSDIR: J1.10 (BUSDIR), U2.31 (IO46)
CLOCK: J1.42 (CLOCK)
D0: J1.34 (D0), U2.20 (IO19), U3.11 (D0)
D1: J1.33 (D1), U2.37 (IO53), U3.12 (D1)
D2: J1.36 (D2), U2.19 (IO20), U3.13 (D2)
D3: J1.35 (D3), U2.39 (IO57), U3.15 (D3)
D4: J1.38 (D4), U2.18 (IO21), U3.16 (D4)
D5: J1.37 (D5), U2.41 (IO64), U3.17 (D5)
D6: J1.40 (D6), U2.11 (IO3), U3.18 (D6)
D7: J1.39 (D7), U2.29 (IO41), U3.19 (D7)
GNDREF: C1.2, C2.2, C3.1, C4.1, C5.1, C6.1, C7.1, C8.-, J1.41 (GND@1), J1.43 (GND@2), J2.2, J2.10, J4.6, LED1.K (C), R1.1, U1.1 (ADJ), U2.10 (GND@2), U2.17 (GND@3), U2.22 (GND@4), U2.30 (GND@5), U2.36 (GND@6), U2.42 (GND@1), U3.14 (GND)
MEM_A14: J3.4, J3.6, U3.1 (A14)
unnamed: J1.44 (SW@1), J1.46 (SW@2)
unnamed: LED1.A, R7.1
SPI_CLK: JP4.2 (C), R7.2, U2.8 (IO5)
SPI_CS: JP3.2 (C), U2.9 (IO4)
SPI_MISO: JP6.2 (C), U2.4 (IO16)
SPI_MOSI: JP5.2 (C), U2.6 (IO11)
SPI_RDY: J4.22, U2.40 (IO62)
TCK: J2.1, R1.2, U2.32 (IO48/TCK)
TDI: J2.9, R4.2, U2.7 (IO8/TDI)
TDO: J2.3, R2.2, U2.38 (IO56/TDO)
TMS: J2.5, R3.2, U2.13 (IO32/TMS)
nSPI_CLK: J4.23, JP4.3 (B)
nSPI_CS: J4.24, JP3.3 (B)
nSPI_MISO: J4.21, JP6.3 (B)
nSPI_MOSI: J4.19, JP5.3 (B)
oSPI_CLK: J4.38, JP4.1 (A)
oSPI_CS: J4.40, JP3.1 (A)
oSPI_MISO: J4.32, JP6.1 (A)
oSPI_MOSI: J4.36, JP5.1 (A)
/CS1: J1.1 (~CS1)
/CS2: J1.2 (~CS2)
/CS12: J1.3 (~CS12)
/INT: J1.8 (~INT)
/IORQ: J1.11 (~IORQ), U2.27 (IO37)
/M1: J1.9 (~M1)
/MEM_CE: J3.2, R6.1, U3.20 (~CS)
/MREQ: J1.12 (~MREQ)
/RD: J1.14 (~RD), U2.26 (IO36), U3.22 (~OE)
/RESET: J1.15 (~RESET)
/RFSH: J1.6 (~RFSH)
/SLTSL: J1.4 (~SLTSL), J3.1
/WAIT: J1.7 (~WAIT), U2.28 (IO40)
/WR: J1.13 (~WR), R5.1, U2.5 (IO14), U3.27 (~WE)

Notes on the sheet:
Decoupling capacitors for the EEPROM (5V) and CPLD (3v)
Flashing Led, driven by the SPI_Clock signal.
Jumpers to select ROM Bank, and enable the EEPROM for writing. J2 is optional (may be permanently closed with solder) since write protection is controlled via software.
EEPROM that can be re-written by software using the AT28C256 programming software from the MSX-DOS prompt
Pullups for the EEPROM Control signals
MSXPi Interface V1.1 Rev.0 RCC @ 2017 - 2023 MSXPi interface - connect MSX computer to Raspberry Pi EEPROM AT28C256 re-writeatable from MSX-DOS EEPROM software: https://github.com/costarc/msxcart_flash32k 2023-04-15
MSX Edge connector (Cartridge)
Connector for the USB-Blaster to program the CPLD
Voltage converter 5v to 3.3v to power the CPLD
CPLD to decode MSX BUS and serial-paralell conversion between MSX and Rasberry Pi

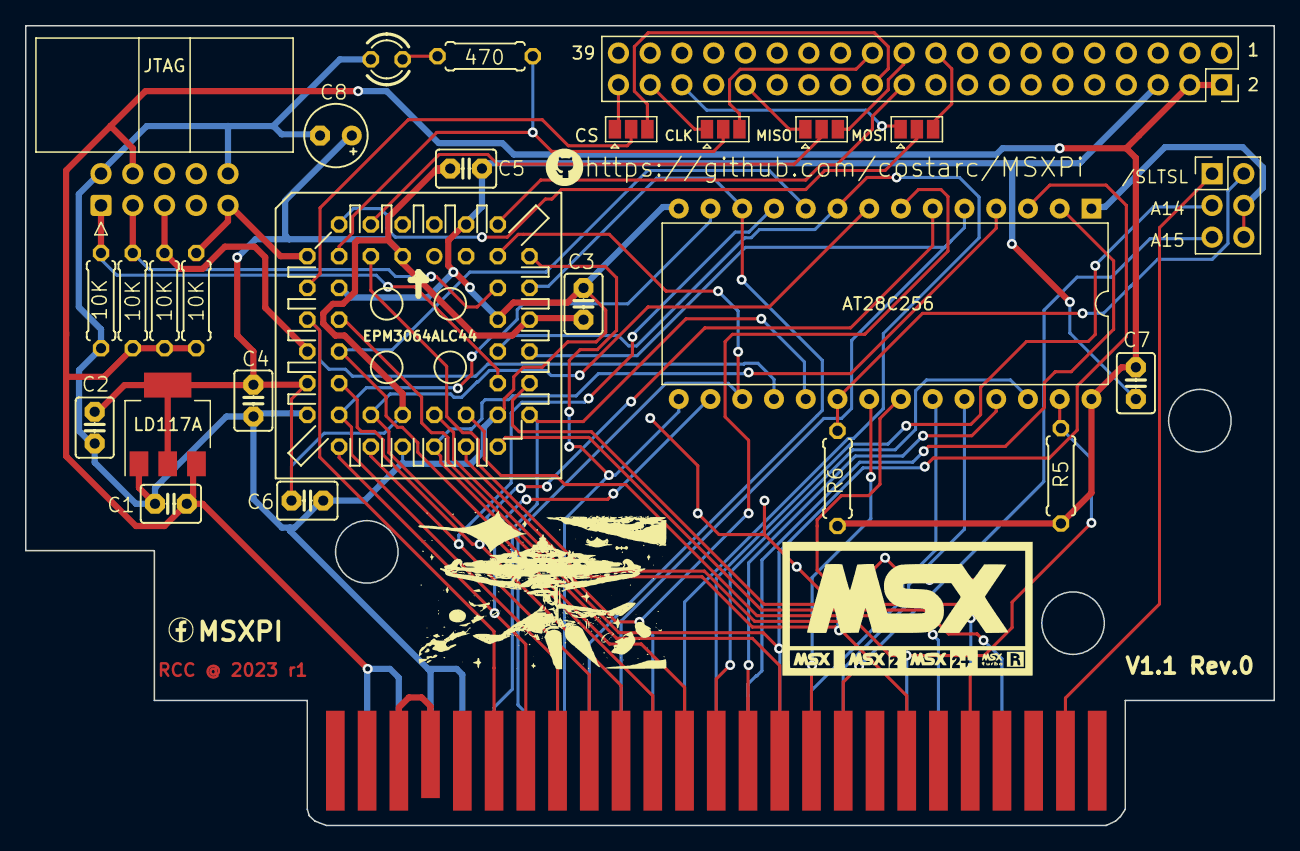
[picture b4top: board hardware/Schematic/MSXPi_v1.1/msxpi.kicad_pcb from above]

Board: 2 copper layers, 99.9 x 64.0 mm, 27 parts (0 on the bottom side), 54 nets.

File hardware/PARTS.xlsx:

R1 | 10k Ohm
R2 | 10k Ohm
R3 | 10k Ohm
R4 | 10k Ohm
R5 | 10k Ohm
R6 | 10k Ohm
R7 | 470 oHM
LE | 3mm, 3.3v
C1,C2,C3,C4,C5,C6,C7 | 0.1uF (ceramic capacitor, code 104)
C8 | 100uF 16v (electrolytic capacitor)
U1 | LD117AS33TR 3.3v Voltage Regulator
U2 | CPLD Altera EPM3064ALC44-10N
U3 | EPROM 27C256
J1 | Pin Header (Male, 2x3 pins)
J2 | JTAG Male conector (10 x PinHead or 90 degree 10xPinHead)
J3 | Pin Socket (Female, 2x20 Pins)
